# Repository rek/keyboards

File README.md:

# Keebs

build notes and config for any keyboards i build

## KiCad:

A nice intro: https://youtu.be/8WXpGTIbxlQ?si=IPm6OvvAeKLTbCmh

JLC Fabrication Toolkik Plugin

- Export Gerber

## Firmware notes

Make sure you are running python 3.8+

```sh
python3 -m pip install --user qmk
apt install gcc-arm-none-eabi avrdude dfu-programmer dfu-util
pip install -U Pillow
qmk setup
qmk list-keyboards | grep xxx
```

Then don't forget: https://docs.qmk.fm/faq_build#linux-udev-rules

## Troubleshooting

- Cannot find the device?
  - Make sure you are using a data USB cable
  - Try USB-A not USB-C
    - For example Arduino Nano will not show up using a C-C cable

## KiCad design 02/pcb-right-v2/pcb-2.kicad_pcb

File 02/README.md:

# Keyboard 02 — aximi

Inspired by: https://github.com/sadekbaroudi/fingerpunch/tree/master/keyboards/ximi/v1

Split 42-key Kailh Choc V1 keyboard. Two Pro Micro (atmega32u4) halves over TRRS serial.

---

## PCB history

### PCB v1 (`pcb/`)

Original single-sided design. Worked well as a left half. No dedicated right PCB.

### PCB v2 (`pcb-left-v1/`, `pcb-right-v1/`)

Intended to be a proper left + right pair. Due to a mirroring error in KiCad the
"right" PCB was generated with all components on the wrong copper layers, making it
effectively a second left. This version went into production — **many copies exist**.

The `pcb-right-v1/` files in this repo have since been corrected (F.Cu ↔ B.Cu layer
swap so hotswap sockets sit on F.Cu and the Pro Micro/TRRS/diodes on B.Cu), but the
boards already ordered match the original two-lefts layout.

### PCB v3 (next production run)

Uses the corrected `pcb-right-v1/` files. True left + right pair, assembles without
any firmware workarounds.

### PCB v4 (`pcb-v4/`) — in progress

Based on the v3 left half. Key change: switching to a reversible Kailh Choc V1 hotswap
footprint (`Kailh_socket_PG1350_reversible`) so the hotswap socket can be soldered on
either side of the board, making a single PCB usable as either left or right half.

**Status:** all 21 switch footprints swapped to `Library:Kailh_socket_PG1350_reversible`
(pads 1 & 2 on both F.Cu and B.Cu). Existing traces will show DRC errors at old pad
positions — open in KiCad, re-route the switch connections, then export Gerbers.

**Next step:** also swap MCU (Pro Micro) and TRRS footprints to reversible variants
(same approach as Lily58), so one PCB truly serves as either half with no orientation
constraint.

---

## Firmware history

### `qmk-v2/` — for PCB v2 (two-lefts production boards)

Because the physical "right" PCB is a left PCB used upside-down, the column pins read
in reverse order on that half. `MATRIX_COL_PINS` is set to `{ B3, B1, F7, F6, F5, F4 }`
(reversed) to compensate. **Keep this config** — it's the correct firmware for all
existing v2 boards.

Flash the left half:
```sh
cd ~/dev/forks/vial-qmk
QMK_HOME=$PWD qmk flash -kb handwired/aximi -km vial -bl avrdude-split-left
```

Flash the right half (which is physically a second left):
```sh
QMK_HOME=$PWD qmk flash -kb handwired/aximi -km vial -bl avrdude-split-right
```

### `qmk-v3/` — for PCB v3 (corrected boards, not yet printed)

Target firmware for the v3 production run. Should not need the column-reversal
workaround since the PCB is properly mirrored. Verify by testing the right half
once assembled before finalising the keymap.

---

## Hardware

### Controller
- Pro Micro (atmega32u4, caterina bootloader)

### Switches
- Kailh Choc Low Profile 1350 (v1) — Crystal Red

### Split link
- TRRS — single serial data wire (`D1`), other two pins VCC/GND

### Trackball (future)
- PMW3360 sensor via SPI — not yet implemented

---

## KiCad

Arduino nano footprint from: https://github.com/g200kg/kicad-lib-arduino

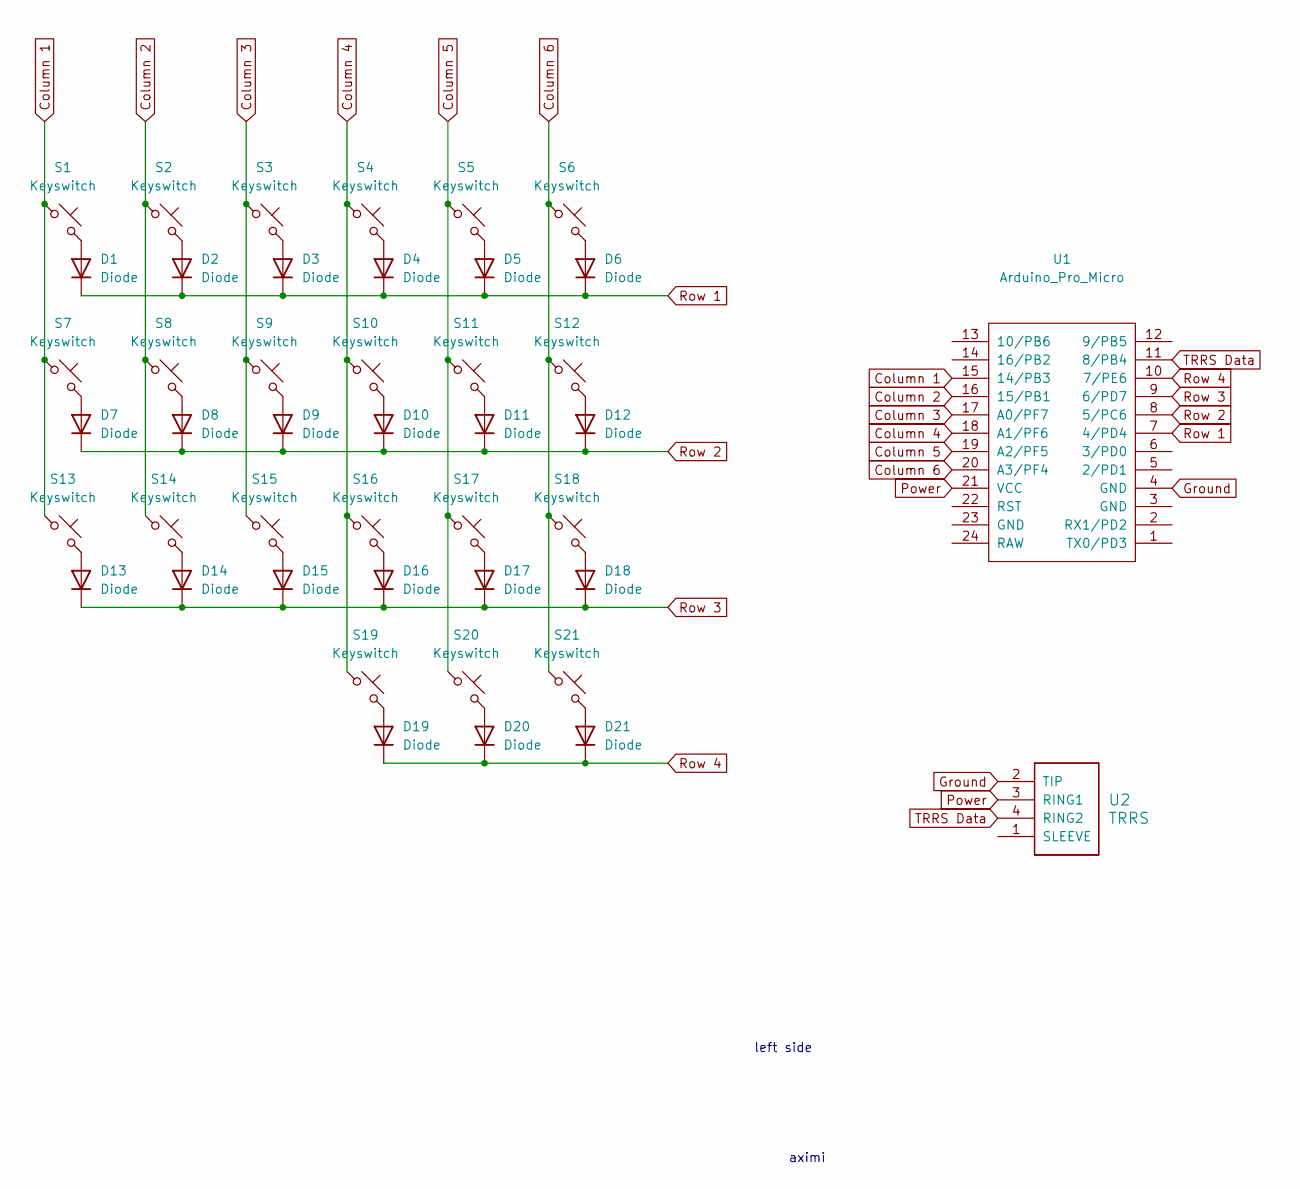
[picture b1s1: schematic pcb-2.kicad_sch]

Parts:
D1, D2, D3, D4, D5, D6, D7, D9, D10, D11, D12, D13, D14, D15, D16, D17, D18, D19, D20, D21: Diode; Diode_SOD-123
D8: Diode; D_SOD-123
S1, S2, S3, S4, S5, S6, S7, S8, S9, S10, S11, S12, S13, S14, S15, S16, S17, S18, S19, S20, S21: Keyswitch; SW_Hotswap_Kailh_Choc_V1
U1: Arduino_Pro_Micro
U2: TRRS; TRRS_PJ-320A

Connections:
Column 1: S1.1, S7.1, S13.1, U1.15 (14/PB3)
Column 2: S2.1, S8.1, S14.1, U1.16 (15/PB1)
Column 3: S3.1, S9.1, S15.1, U1.17 (A0/PF7)
Column 4: S4.1, S10.1, S16.1, S19.1, U1.18 (A1/PF6)
Column 5: S5.1, S11.1, S17.1, S20.1, U1.19 (A2/PF5)
Column 6: S6.1, S12.1, S18.1, S21.1, U1.20 (A3/PF4)
Ground: U1.4 (GND), U2.2 (TIP)
unnamed: D1.2 (A), S1.2
unnamed: D2.2 (A), S2.2
unnamed: D3.2 (A), S3.2
unnamed: D4.2 (A), S4.2
unnamed: D5.2 (A), S5.2
unnamed: D6.2 (A), S6.2
unnamed: D7.2 (A), S7.2
unnamed: D8.2 (A), S8.2
unnamed: D9.2 (A), S9.2
unnamed: D10.2 (A), S10.2
unnamed: D11.2 (A), S11.2
unnamed: D12.2 (A), S12.2
unnamed: D13.2 (A), S13.2
unnamed: D14.2 (A), S14.2
unnamed: D15.2 (A), S15.2
unnamed: D16.2 (A), S16.2
unnamed: D17.2 (A), S17.2
unnamed: D18.2 (A), S18.2
unnamed: D19.2 (A), S19.2
unnamed: D20.2 (A), S20.2
unnamed: D21.2 (A), S21.2
Power: U1.21 (VCC), U2.3 (RING1)
Row 1: D1.1 (K), D2.1 (K), D3.1 (K), D4.1 (K), D5.1 (K), D6.1 (K), U1.7 (4/PD4)
Row 2: D7.1 (K), D8.1 (K), D9.1 (K), D10.1 (K), D11.1 (K), D12.1 (K), U1.8 (5/PC6)
Row 3: D13.1 (K), D14.1 (K), D15.1 (K), D16.1 (K), D17.1 (K), D18.1 (K), U1.9 (6/PD7)
Row 4: D19.1 (K), D20.1 (K), D21.1 (K), U1.10 (7/PE6)
TRRS Data: U1.11 (8/PB4), U2.4 (RING2)

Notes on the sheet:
aximi
left side

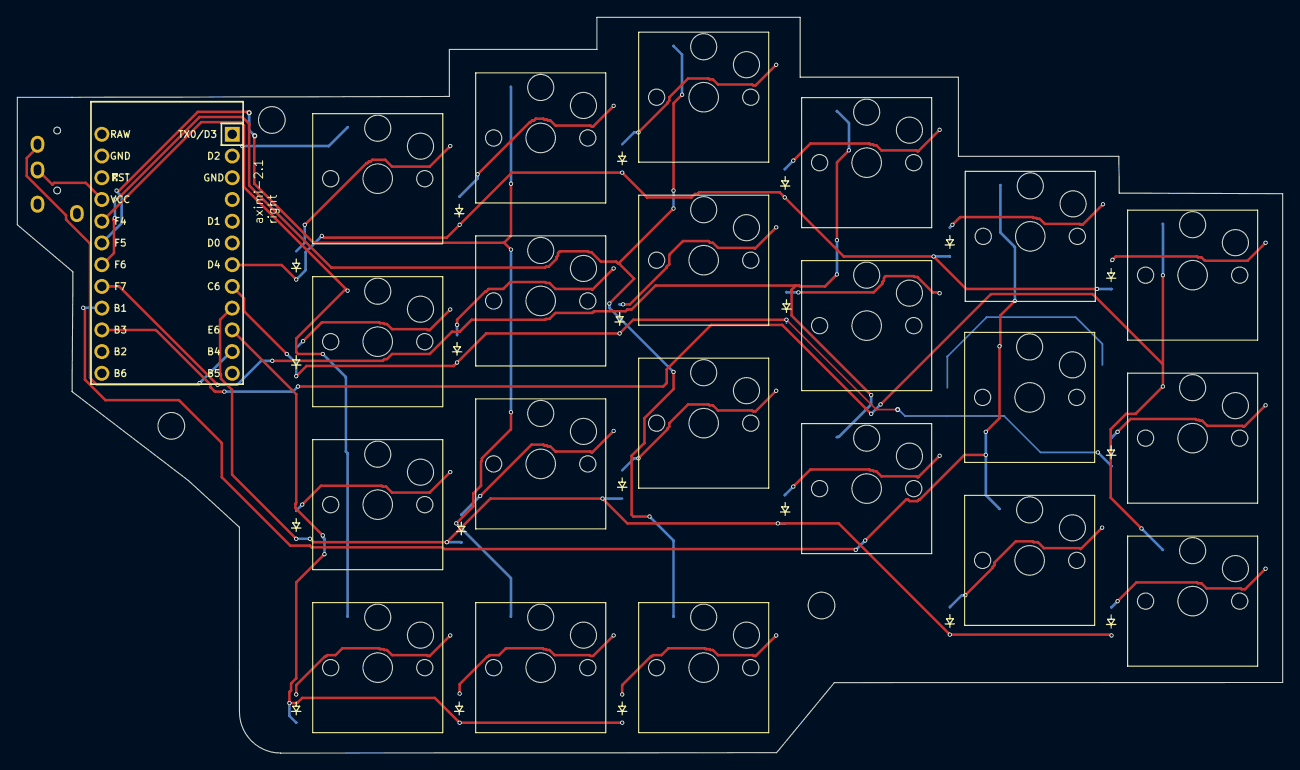
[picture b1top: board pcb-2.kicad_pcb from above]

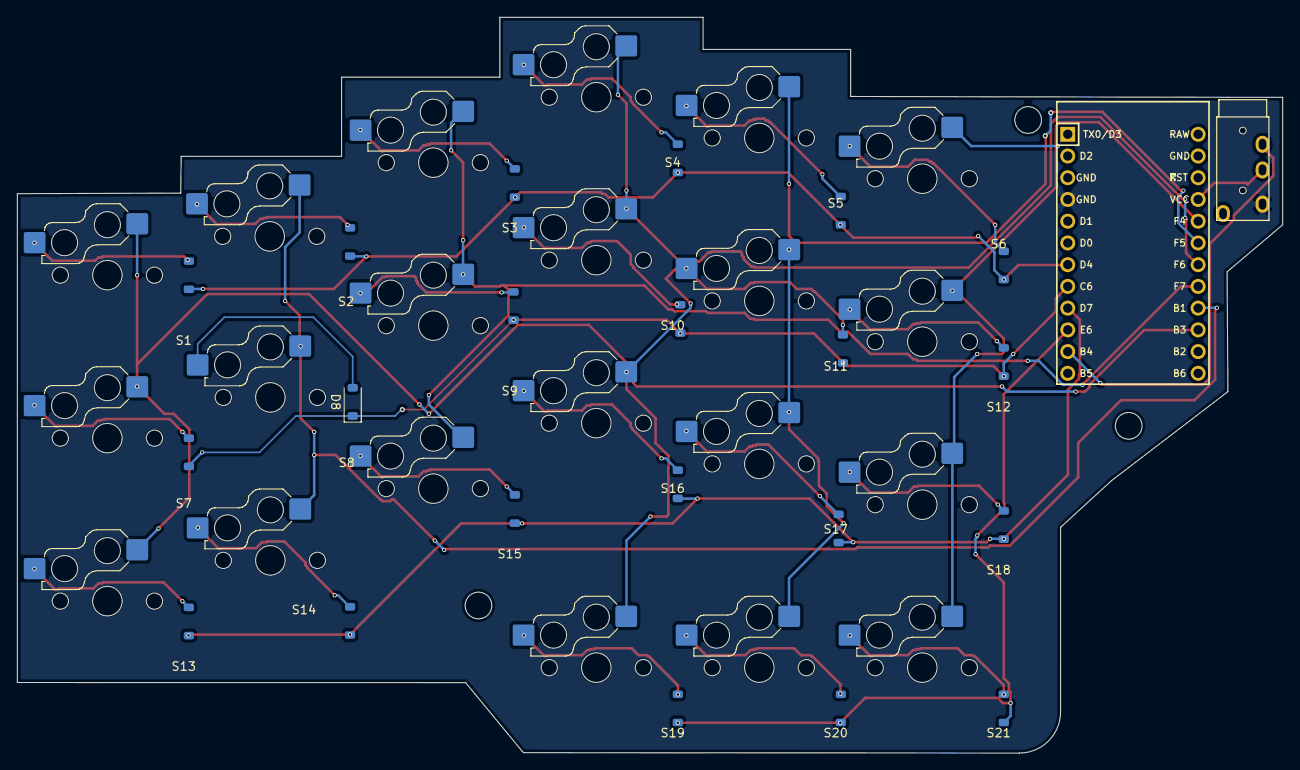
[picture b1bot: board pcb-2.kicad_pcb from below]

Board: 2 copper layers, 147.9 x 86.0 mm, 44 parts (23 on the bottom side), 34 nets.

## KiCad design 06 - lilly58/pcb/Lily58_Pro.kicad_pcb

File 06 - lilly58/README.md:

# 06 — Lily58 Pro (ZMK, two firmware variants)

A split 58-key Lily58 **Pro** keyboard running **ZMK** on a **nice!nano v2** (a
"ProMicro nRF52840" clone, see `pro-micro-nice-clone.png`) per half. The same
hardware runs either of two firmware variants:

| Variant | Folder | Halves talk over | PC talks to the left over | Power |
|---|---|---|---|---|
| **06a** — Bluetooth | `zmk-config/06a-ble/` | Bluetooth | USB or Bluetooth | LiPo per half |
| **06b** — TRRS wired (current) | `zmk-config/06b-wired/` | TRRS cable | USB only | Left on USB; right fed through the cable |

The 06b hardware rework (W1 cut + two jumper wires per half) doesn't affect
06a, so you can flash either variant at any time.

> **To build/flash firmware, follow [`BUILDING.md`](BUILDING.md)** — the canonical, journey-free procedure.
> Bring-up history and hard-won learnings: [`HANDOFF.md`](HANDOFF.md). Fault finding: [`TROUBLESHOOTING.md`](TROUBLESHOOTING.md).

## At a glance

| | |
|---|---|
| **Board** | Lily58 **Pro** (Pro Micro footprint + Kailh hotswap sockets) |
| **PCB design source** | `~/dev/keyboard-clones/Lily58/Pro/PCB/Lily58_Pro.kicad_pcb` |
| **Fabbed gerbers** | `pcb/production/` (front copper + edge cuts) — board renders in `pcb/` |
| **Controller** | nice!nano v2 (nRF52840) → firmware is **ZMK**, not QMK |
| **Firmware** | `zmk-config/06a-ble/` and `zmk-config/06b-wired/`, shared `zmk-config/build-flash.sh` |
| **Case** | `case/v1/` STLs |
| **Matrix** | 5 rows × 6 cols per half |
| **Status** | ✅ **06b working end-to-end** (2026-11-01): both halves over TRRS, left on USB, **ZMK Studio** for live key editing. 06a verified 2026-07-06 (Bluetooth + batteries). |

## ⚠️ The big gotcha: the controllers sit in the reversed hole-set

The Lily58 Pro controller footprint is **reversible** — two staggered hole-sets
per side. **Both nice!nanos are soldered into the "swapped" set**, which swaps
the controller's two pin rows. Every footprint net therefore lands on a
different nice!nano pin than the PCB intends:

- **Key matrix:** rows and cols swap. Fixed in firmware (no desoldering) by the
  kscan remap in each variant's `config/lily58.keymap`:

  | | row0–4 | col0–5 |
  |---|---|---|
  | stock shield | pro_micro `5,6,7,8,9` (D5–D9) | `19,18,15,14,16,10` |
  | **our left remap** | pro_micro `18,15,14,16,10` (D18,D15,D14,D16,D10) | `4,5,6,7,8,9` (D4–D9) |
  | **our right remap** | same rows | `9,8,7,6,5,4` (mirrored) |

- **TRRS jack (J2):** its power and DATA lines hit the wrong controller pins.
  Harmless for 06a (Bluetooth never uses the jack). 06b needs the hardware
  rework below.

## 06b: wired split (TRRS)

ZMK's wired split is full-duplex UART, so it needs **two** data wires. Because
of the reversed hole-set, J2's lines actually reach:

| J2 pad | PCB net | Really hits on the nice!nano |
|---|---|---|
| 1 | VCC | GND |
| 2 | GND | VCC 3.3V (and RST, P0.08) |
| 3 | DATA | GND, through the W1 jumper — unusable as is |
| 4 | — (P1 pad only) | nothing until hand-wired |

**Rework, on both halves** (picture: [`trrs-rework-guide.png`](trrs-rework-guide.png);
step-by-step: [`BUILDING.md`](BUILDING.md#06b-trrs-hardware-rework-one-time)):

1. Wire **P1** to controller hole **6** (nice!nano **P0.29**).
2. **Cut W1** (top side, next to P1/P2) so DATA is no longer grounded.
3. Wire J2's **DATA leg** to controller hole **5** (nice!nano **P0.31**).

The firmware pins live in
[`zmk-config/06b-wired/config/lily58-wired-pins.h`](zmk-config/06b-wired/config/lily58-wired-pins.h):
left sends on P0.31 and listens on P0.29; the right is the mirror.

- **Use a 4-contact TRRS cable**, not a 3-contact TRS one (its sleeve bridges two jack contacts).
- **Never plug or unplug the TRRS cable while either half has power** (USB or
  battery). ZMK's docs warn it can permanently damage the controllers.
- The right half is powered through the cable (pads 1/2 tie the two halves'
  GND and 3.3V rails). Switch its battery off or remove it.
- Bluetooth is off (`CONFIG_ZMK_BLE=n`), so there are no bonds, no output
  endpoint to get stuck, and no host battery readout.

## Build & flash

Local toolchain lives at `~/dev/zmk-workspace` (west venv + ZMK `main`, uses
system `arm-none-eabi-gcc`, no Zephyr SDK).

```sh
# from this folder; first argument picks the variant:
zmk-config/build-flash.sh 06b left      # build + flash left half (TRRS)
zmk-config/build-flash.sh 06b right     # right half
zmk-config/build-flash.sh 06a left      # same, Bluetooth variant
```

To flash: double-tap RESET on the target nice!nano so the `NICENANO` drive
appears, then run the command. It picks the drive by USB serial, so it never
flashes the wrong half. Full details in [`BUILDING.md`](BUILDING.md).

A cloud build of both variants runs at repo root: `.github/workflows/lilly58.yml`.

## Battery (06a)

The Lily58 Pro has **no battery provision** (it's a wired design). The LiPo wires directly to the nice!nano's **`B+` / `B-`** pads (at the USB end, overhanging the top board edge).

- **Polarity is critical:** red → `B+`, black → `B-`. Reversing kills the nice!nano.
- nice!nano charges the cell over USB at **~100 mA** (no separate charger). Bigger cell = longer charge (750 mAh ≈ 7–8 h).
- Any capacity works electrically (110–1000 mAh+); limited only by **case space** + charge time. ZMK sips power → weeks–months per charge.
- Recommended: a small **slide switch** in series with one battery lead for a true power-off.
- Use thin 30 AWG / magnet wire; secure the cell so it can't be punctured.
- ❌ Do **not** wire the battery to `RAW`/`GND` — that bypasses charging.

To show both halves' charge in a desktop status bar, see
[`HOST-BATTERY.md`](HOST-BATTERY.md) — the right half is proxied as a second BLE
battery service and needs a GATT walk to read, and there is **no** battery
readout over USB at all.

## What the extra PCB holes are

Near the controller: `RESET` (reset button), and the **I²C section** — `R1`/`R2`
(SDA/SCL pull-up resistors), `P1`/`P2` (breakout pads), `W1` (DATA solder
jumper), `J2` (TRRS jack, `MJ-4PP-9`). `J2`, `P1` and `W1` are used by the 06b
rework. `R1`/`R2` are only needed for the I²C **OLED** screen (then also enable
`CONFIG_ZMK_DISPLAY` in `lily58.conf`) — but with the reversed hole-set, SDA/SCL
land on P0.31/P0.29, which 06b now uses for the split link.

## To-do

- [ ] Check the solder joints on the few dead keys.
- [ ] Mirror the ZMK Studio edits (e.g. the right inner key) back into
      `06b-wired/config/lily58.keymap`, so a rebuild or reset doesn't lose them.
- [ ] Verify battery runtime on 06a.
- [ ] Optional: move the kscan overrides into the `lily58_*.overlay` files
      (more idiomatic than in `.keymap`).

## Debugging notes (full detail in [`HANDOFF.md`](HANDOFF.md) and [`TROUBLESHOOTING.md`](TROUBLESHOOTING.md))

- **Label the halves L/R.** Each half's USB serial (left `3A8F02D9AD37EF58`,
  right `EC93E089067872A6`) is the same in bootloader mode, which is how
  `build-flash.sh` tells them apart.
- **Charge-only cables** = board powers (LED on) but nothing enumerates on USB
  (not even the bootloader drive). Use a known data cable, straight to the PC.
- **A peripheral (right) doesn't type over USB alone** — test it with the
  central. The `CONFIG_ZMK_SPLIT=n` standalone trick gives **false negatives**.
- **06b link dead?** `build-flash.sh <variant> <side> --log` builds a USB-logging
  image. The right logs every split message it sends; the left logs anything it
  receives (even garbage). See `BUILDING.md`.
- **06a: output endpoint (USB vs BLE) persists in flash and survives reflashing.**
  Fix with `&out OUT_USB` or the `settings_reset` shield, not reflashing.

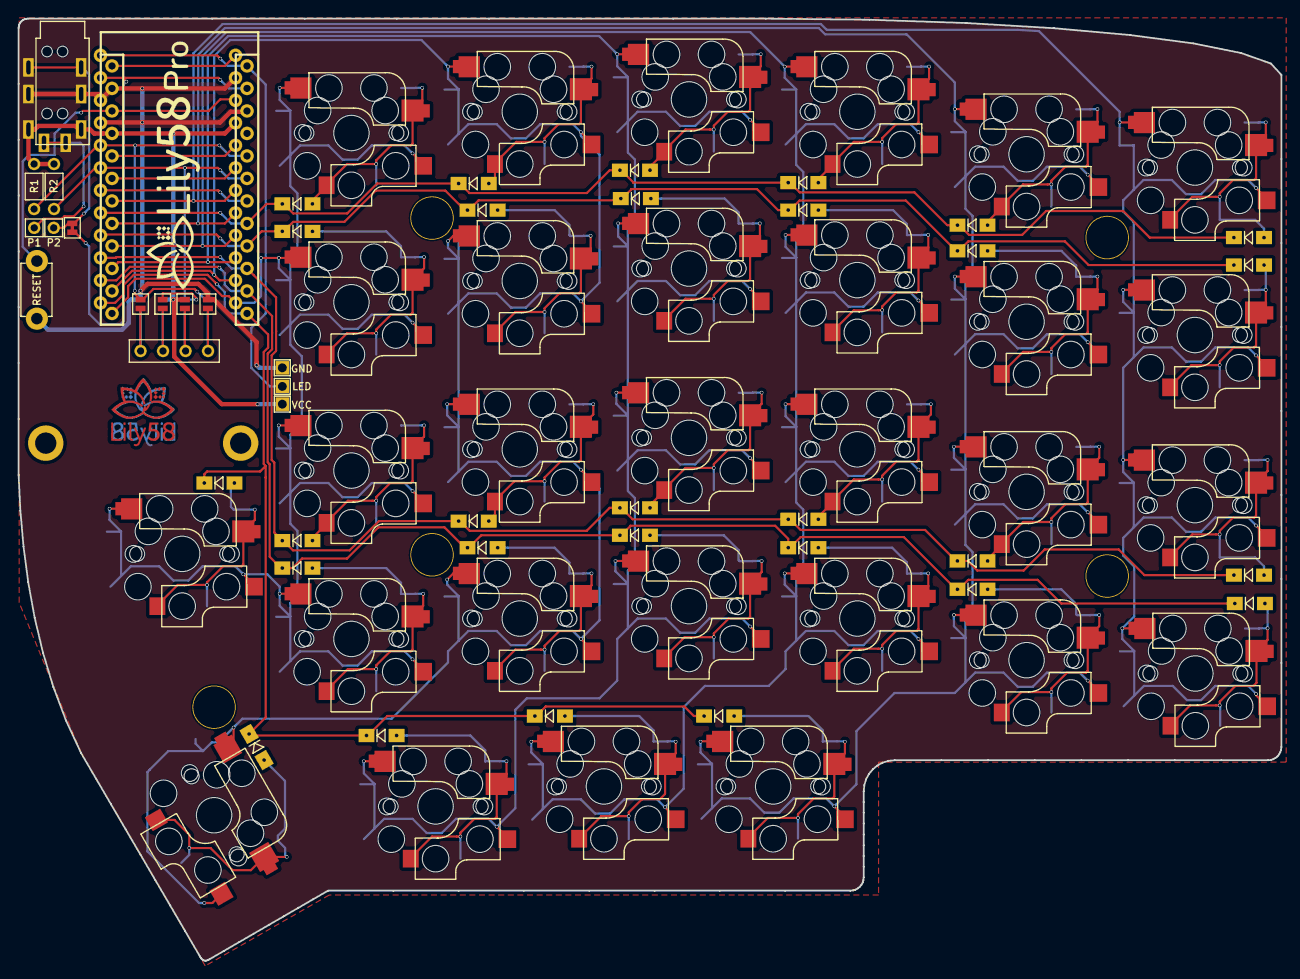
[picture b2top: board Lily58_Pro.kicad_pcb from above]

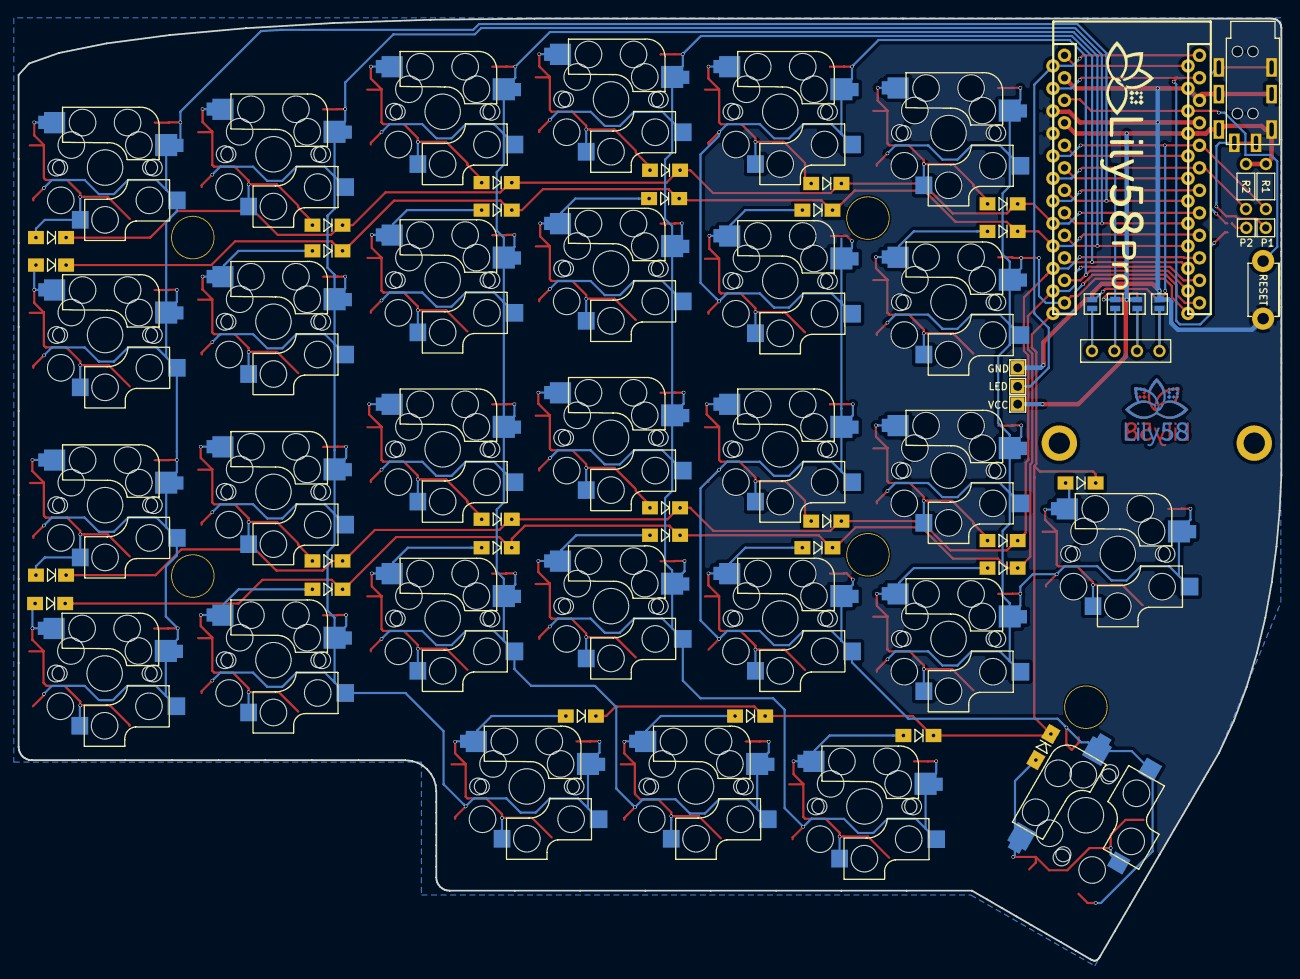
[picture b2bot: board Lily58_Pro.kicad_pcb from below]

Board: 2 copper layers, 142.5 x 106.3 mm, 83 parts (4 on the bottom side), 53 nets.

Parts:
D1, D2, D3, D4, D5, D6, D7, D8, D9, D10, D11, D12, D13, D14, D15, D16, D17, D18, D19, D20, D21, D22, D23, D24, D25, D26, D27, D28, D29: D; Diode_SOD123
J1: LED
J2: 4PIN; MJ-4PP-9
J3: OLED; OLED_4Pin
JP1, JP2, JP3, JP4, JP5, JP6, JP7, JP8: Jumper
P1, P2: i2c_pin; 1pin_conn
R1, R2: R; RESISTOR_mini
RSW1: SW_RST; TACT_SWITCH_TVBP06
SW1, SW2, SW3, SW4, SW5, SW6, SW7, SW8, SW9, SW10, SW11, SW12, SW13, SW14, SW15, SW16, SW17, SW18, SW19, SW20, SW21, SW22, SW23, SW24, SW25, SW26, SW27, SW28, SW29: SW_PUSH; CherryMX_KailhLowProfile_Hotswap_edge
TH1, TH2: HOLE; M2_HOLE_PCB
TH3, TH4, TH5, TH6, TH7: HOLE; HOLE_M2_TH
U1: ProMicro; ProMicro_rev2
W1: jumper; jumper_data

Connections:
DATA: U1.2, W1.1
GND: J1.3, J2.2, JP1.2, JP8.2, RSW1.1, U1.3, U1.4, U1.23
LED: J1.2, U1.1
unnamed: D1.2, SW1.2
unnamed: D2.2, SW2.2
unnamed: D3.2, SW3.2
unnamed: D4.2, SW4.2
unnamed: D5.2, SW5.2
unnamed: D6.2, SW6.2
unnamed: D7.2, SW7.2
unnamed: D8.2, SW8.2
unnamed: D9.2, SW9.2
unnamed: D10.2, SW10.2
unnamed: D11.2, SW11.2
unnamed: D12.2, SW12.2
unnamed: D13.2, SW13.2
unnamed: D14.2, SW14.2
unnamed: D15.2, SW15.2
unnamed: D16.2, SW16.2
unnamed: D17.2, SW17.2
unnamed: D18.2, SW18.2
unnamed: D19.2, SW19.2
unnamed: D20.2, SW20.2
unnamed: D21.2, SW21.2
unnamed: D22.2, SW22.2
unnamed: D23.2, SW23.2
unnamed: D24.2, SW24.2
unnamed: D25.2, SW25.2
unnamed: D26.2, SW26.2
unnamed: D27.2, SW27.2
unnamed: D28.2, SW28.2
unnamed: D29.2, SW29.2
unnamed: J2.3, P2.1, W1.2
unnamed: J2.4, P1.1
unnamed: J3.1, JP4.1, JP8.1
unnamed: J3.2, JP3.1, JP7.1
unnamed: J3.3, JP2.1, JP6.1
unnamed: J3.4, JP1.1, JP5.1
RESET: RSW1.2, U1.22
SCL: JP3.2, JP6.2, R2.2, U1.6
SDA: JP4.2, JP5.2, R1.2, U1.5
VCC: J1.1, J2.1, JP2.2, JP7.2, R1.1, R2.1, U1.21
col0: SW6.1, SW12.1, SW18.1, SW24.1, U1.18
col1: SW5.1, SW11.1, SW17.1, SW23.1, SW29.1, U1.17
col2: SW4.1, SW10.1, SW16.1, SW22.1, SW28.1, U1.16
col3: SW3.1, SW9.1, SW15.1, SW21.1, SW27.1, U1.15
col4: SW2.1, SW8.1, SW14.1, SW20.1, SW26.1, U1.14
col5: SW1.1, SW7.1, SW13.1, SW19.1, SW25.1, U1.13
row0: D1.1, D2.1, D3.1, D4.1, D5.1, D6.1, U1.8
row1: D7.1, D8.1, D9.1, D10.1, D11.1, D12.1, U1.9
row2: D13.1, D14.1, D15.1, D16.1, D17.1, D18.1, U1.10
row3: D19.1, D20.1, D21.1, D22.1, D23.1, D24.1, U1.11
row4: D25.1, D26.1, D27.1, D28.1, D29.1, U1.12

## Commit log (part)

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2023-06-26 feat: init
2023-06-27 feat: update images and models
2023-06-27 feat: update readme, add keymap
2023-11-10 feat: update to newiest layout
2024-01-28 feat: add some more changes to my key layout
2024-05-09 feat: start on keeb 2
2024-06-08 feat: update setup info
2024-06-17 feat: adding xixmi config
2024-06-20 feat: qmk for 02
2024-06-20 docs: minor readme additions
2024-06-21 docs: add info about different pin names in the pinout
2024-06-21 feat: better pins
2024-06-29 feat: updated 02 with vial settings
2024-08-25 feat: add working split config
2024-08-30 feat: starting on 4
2024-10-27 chore: test logo
2024-10-27 feat: add splay pcb left
2024-10-27 chore: typo
2024-10-27 feat: closer to final splay config
2024-10-27 feat: splay rules
2024-10-27 feat: add second side for 02
2026-06-17 feat: updated keymaps for 1
